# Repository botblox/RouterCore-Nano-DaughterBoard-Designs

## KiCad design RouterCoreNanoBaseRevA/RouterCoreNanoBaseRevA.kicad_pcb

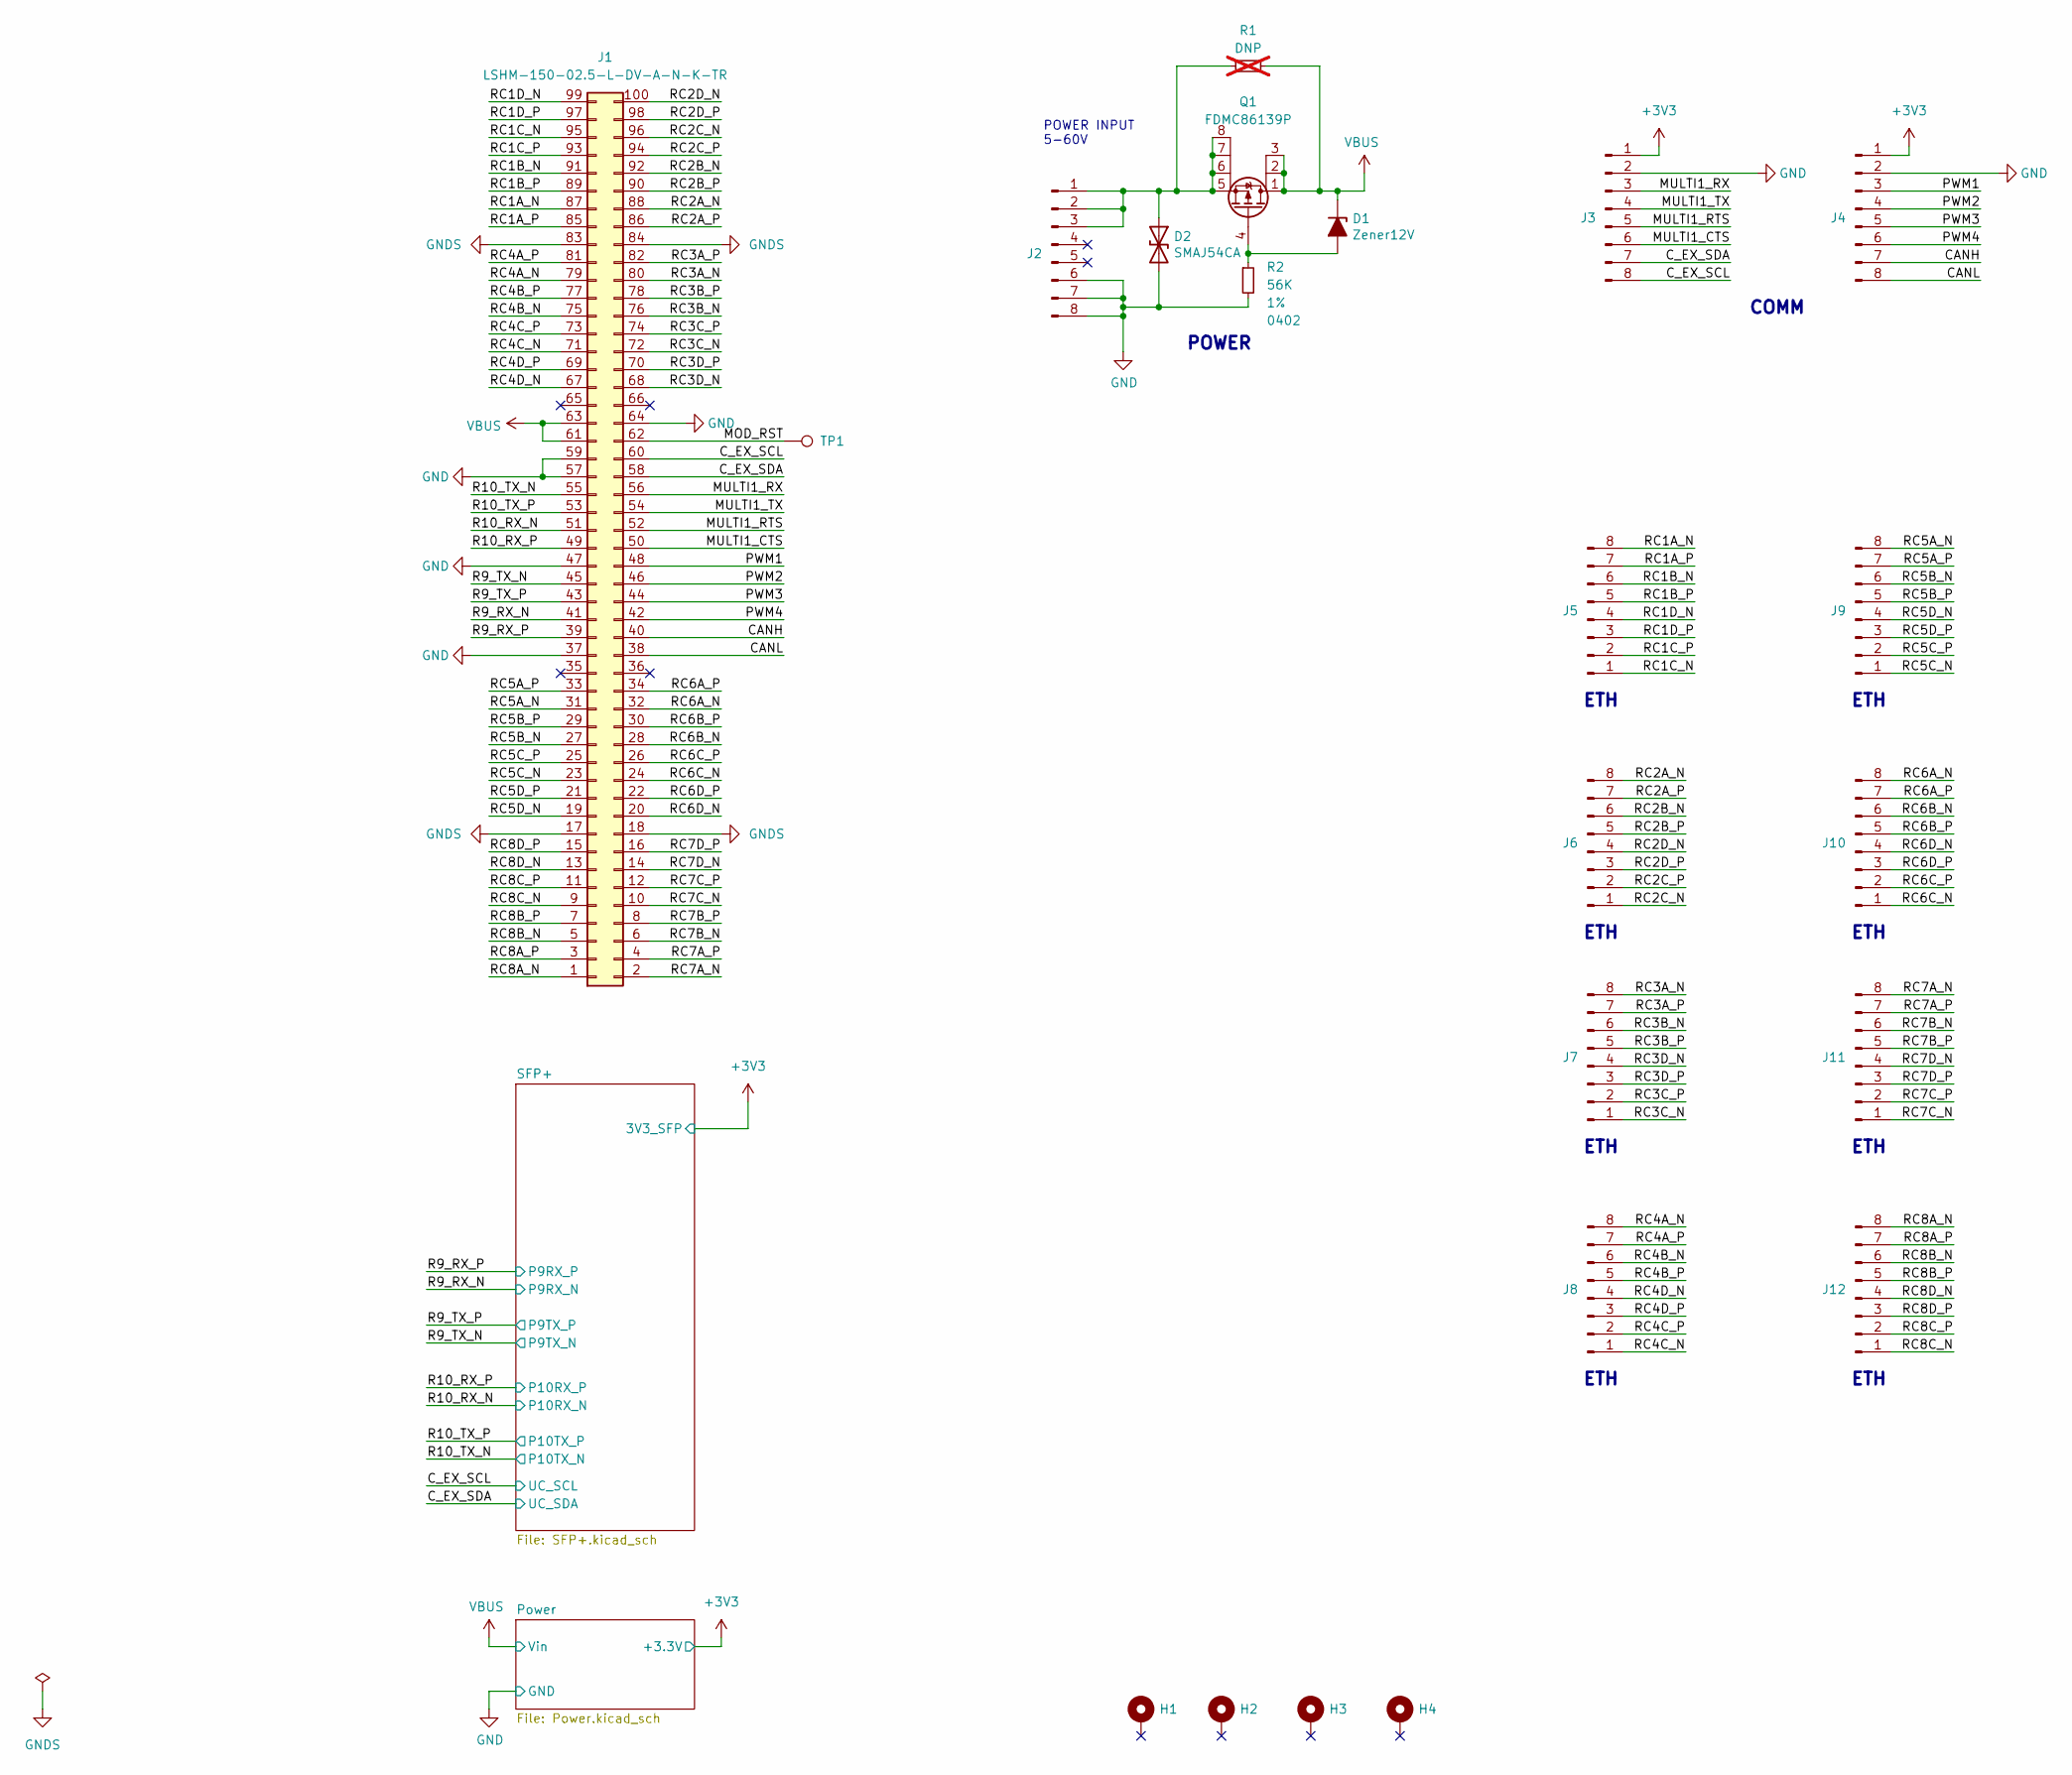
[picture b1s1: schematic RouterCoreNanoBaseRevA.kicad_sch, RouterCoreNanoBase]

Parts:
D1: Zener12V; D_SOD-323; VOLTAGE 12V; MFG1_PART# MM3Z12VT1G; JLC C236177
D2: SMAJ54CA; D_SMA; VOLTAGE 54V; MFG1_PART# SMAJ54CA; JLC C2649855
H1, H2, H3, H4: SMTWE2050MTJ; MountingHole_M2_9774050243R_SMTWE2050MTJ; MFG1_PART# SMTWE2050MTJ; JLC C2928183
J1: LSHM-150-02.5-L-DV-A-N-K-TR; Samtec_LSHM-150-xx.x-x-DV-N_2x50_P0.50mm_Vertical; MFG1_PART# LSHM-150-02.5-L-DV-A-N-K-TR; JLC C2940507
J2, J3, J4, J5, J6, J7, J8, J9, J10, J11, J12: 2147210080; Molex_Zero-Hachi_214721-00XX_1x08_P0.8mm_Horizontal; MFG1_PART# 2147210080; JLC C5492017
Q1: FDMC86139P; VSON-8_3.3x3.3mm_P0.65mm_FDMC86139P; VOLTAGE 100V; MFG1_PART# FDMC86139P; JLC C463243
R1: DNP; R_0603_1608Metric; MFG1_PART# DNP; not fitted
R2: 56K; R_0402_1005Metric; TOLERANCE 1%; MFG1_PART# RC0402FR-0756KL; JLC C114756
TP1: TP; TestPoint_Pad_D1.0mm; MFG1_PART# DNP

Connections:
+3V3: J3.1, J4.1; also elsewhere on the board
/CANH: J1.40, J4.7
/CANL: J1.38, J4.8
/C_EX_SCL: J1.60, J3.8; also elsewhere on the board
/C_EX_SDA: J1.58, J3.7; also elsewhere on the board
/MOD_RST: J1.62, TP1.1
/MULTI1_CTS: J1.50, J3.6
/MULTI1_RTS: J1.52, J3.5
/MULTI1_RX: J1.56, J3.3
/MULTI1_TX: J1.54, J3.4
/PWM1: J1.48, J4.3
/PWM2: J1.46, J4.4
/PWM3: J1.44, J4.5
/PWM4: J1.42, J4.6
/R9_RX_N: J1.41; also elsewhere on the board
/R9_RX_P: J1.39; also elsewhere on the board
/R9_TX_N: J1.45; also elsewhere on the board
/R9_TX_P: J1.43; also elsewhere on the board
/R10_RX_N: J1.51; also elsewhere on the board
/R10_RX_P: J1.49; also elsewhere on the board
/R10_TX_N: J1.55; also elsewhere on the board
/R10_TX_P: J1.53; also elsewhere on the board
/RC1A_N: J1.87, J5.8
/RC1A_P: J1.85, J5.7
/RC1B_N: J1.91, J5.6
/RC1B_P: J1.89, J5.5
/RC1C_N: J1.95, J5.1
/RC1C_P: J1.93, J5.2
/RC1D_N: J1.99, J5.4
/RC1D_P: J1.97, J5.3
/RC2A_N: J1.88, J6.8
/RC2A_P: J1.86, J6.7
/RC2B_N: J1.92, J6.6
/RC2B_P: J1.90, J6.5
/RC2C_N: J1.96, J6.1
/RC2C_P: J1.94, J6.2
/RC2D_N: J1.100, J6.4
/RC2D_P: J1.98, J6.3
/RC3A_N: J1.80, J7.8
/RC3A_P: J1.82, J7.7
/RC3B_N: J1.76, J7.6
/RC3B_P: J1.78, J7.5
/RC3C_N: J1.72, J7.1
/RC3C_P: J1.74, J7.2
/RC3D_N: J1.68, J7.4
/RC3D_P: J1.70, J7.3
/RC4A_N: J1.79, J8.8
/RC4A_P: J1.81, J8.7
/RC4B_N: J1.75, J8.6
/RC4B_P: J1.77, J8.5
/RC4C_N: J1.71, J8.1
/RC4C_P: J1.73, J8.2
/RC4D_N: J1.67, J8.4
/RC4D_P: J1.69, J8.3
/RC5A_N: J1.31, J9.8
/RC5A_P: J1.33, J9.7
/RC5B_N: J1.27, J9.6
/RC5B_P: J1.29, J9.5
/RC5C_N: J1.23, J9.1
/RC5C_P: J1.25, J9.2
/RC5D_N: J1.19, J9.4
/RC5D_P: J1.21, J9.3
/RC6A_N: J1.32, J10.8
/RC6A_P: J1.34, J10.7
/RC6B_N: J1.28, J10.6
/RC6B_P: J1.30, J10.5
/RC6C_N: J1.24, J10.1
/RC6C_P: J1.26, J10.2
/RC6D_N: J1.20, J10.4
/RC6D_P: J1.22, J10.3
/RC7A_N: J1.2, J11.8
/RC7A_P: J1.4, J11.7
/RC7B_N: J1.6, J11.6
/RC7B_P: J1.8, J11.5
/RC7C_N: J1.10, J11.1
/RC7C_P: J1.12, J11.2
/RC7D_N: J1.14, J11.4
/RC7D_P: J1.16, J11.3
/RC8A_N: J1.1, J12.8
/RC8A_P: J1.3, J12.7
/RC8B_N: J1.5, J12.6
/RC8B_P: J1.7, J12.5
/RC8C_N: J1.9, J12.1
/RC8C_P: J1.11, J12.2
/RC8D_N: J1.13, J12.4
/RC8D_P: J1.15, J12.3
GND: D2.2 (A2), J1.37, J1.47, J1.57, J1.59, J1.64, J2.6, J2.7, J2.8, J3.2, J4.2, R2.2; also elsewhere on the board
GNDS: J1.17, J1.18, J1.83, J1.84
unnamed: D1.2 (A), Q1.4 (G), R2.1
unnamed: D2.1 (A1), J2.1, J2.2, J2.3, Q1.5 (D), Q1.6 (D), Q1.7 (D), Q1.8 (D), R1.1
VBUS: D1.1 (K), J1.61, J1.63, Q1.1 (S), Q1.2 (S), Q1.3 (S), R1.2; also elsewhere on the board

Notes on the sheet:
ETH
POWER
COMM
POWER INPUT 5-60V

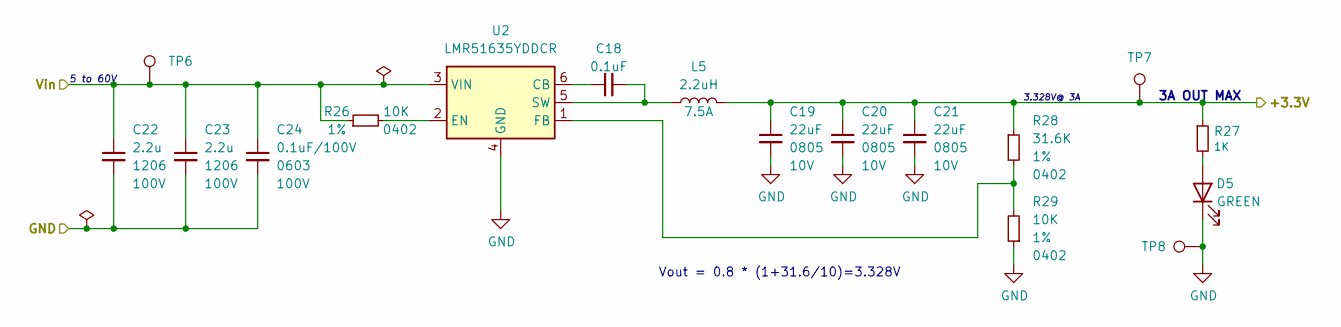
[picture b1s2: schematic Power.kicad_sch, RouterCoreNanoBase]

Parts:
C18: 0.1uF; C_0402_Small; VOLTAGE 50V; TOLERANCE 10%; MFG1_PART# GCM155R71H104KE02D; LCSC# C85858
C19, C20, C21: 22uF; C_0805_2012Metric; VOLTAGE 10V; TOLERANCE 20%; MFG1_PART# GRM21BZ71A226ME15L; LCSC# C907991
C22, C23: 2.2u; C_1206_Small; VOLTAGE 100V; TOLERANCE 10%; MFG1_PART# CL31B225KCHSNNE; LCSC# C170101
C24: 0.1uF/100V; C_0603_Small; VOLTAGE 100V; TOLERANCE 10%; MFG1_PART# CC0603KRX7R0BB104; LCSC# C113803
D5: GREEN; LED_0402_1005Metric; MFG2_PART# APHHS1005CGCK; LCSC# C264408
L5: 2.2uH; L_Sunlord_MWSA0503S; TOLERANCE ±20%; MFG1_PART# MWSA0503S-2R2MT; LCSC# C408408
R26, R29: 10K; R_0402_1005Metric; TOLERANCE 1%; MFG1_PART# RC0402FR-0710KL; LCSC# C60490
R27: 1K; R_0402_1005Metric; TOLERANCE 1%; MFG1_PART# RC0402FR-071KL; LCSC# C106235
R28: 31.6K; R_0402_1005Metric; TOLERANCE 1%; MFG1_PART# RC0402FR-0731K6L; LCSC# C276265
TP6, TP7, TP8: TP; TestPoint_Pad_D1.0mm; MFG1_PART# DNP
U2: LMR51635YDDCR; SOT-23-6; MFG1_PART# LMR51635YDDCR; JLC C45262770

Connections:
+3V3: C19.1, C20.1, C21.1, L5.2, R27.1, R28.1, TP7.1; also elsewhere on the board
GND: C19.2, C20.2, C21.2, C22.2, C23.2, C24.2, D5.1 (K), R29.1, TP8.1, U2.4 (GND); also elsewhere on the board
unnamed: D5.2 (A), R27.2
unnamed: C18.1, U2.6 (CB)
unnamed: R26.2, U2.2 (EN)
unnamed: R28.2, R29.2, U2.1 (FB)
unnamed: C18.2, L5.1, U2.5 (SW)
VBUS: C22.1, C23.1, C24.1, R26.1, TP6.1, U2.3 (VIN); also elsewhere on the board

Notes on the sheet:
3A OUT MAX
5 to 60V
Vout = 0.8 * (1+31.6/10)=3.328V
3.328V@ 3A

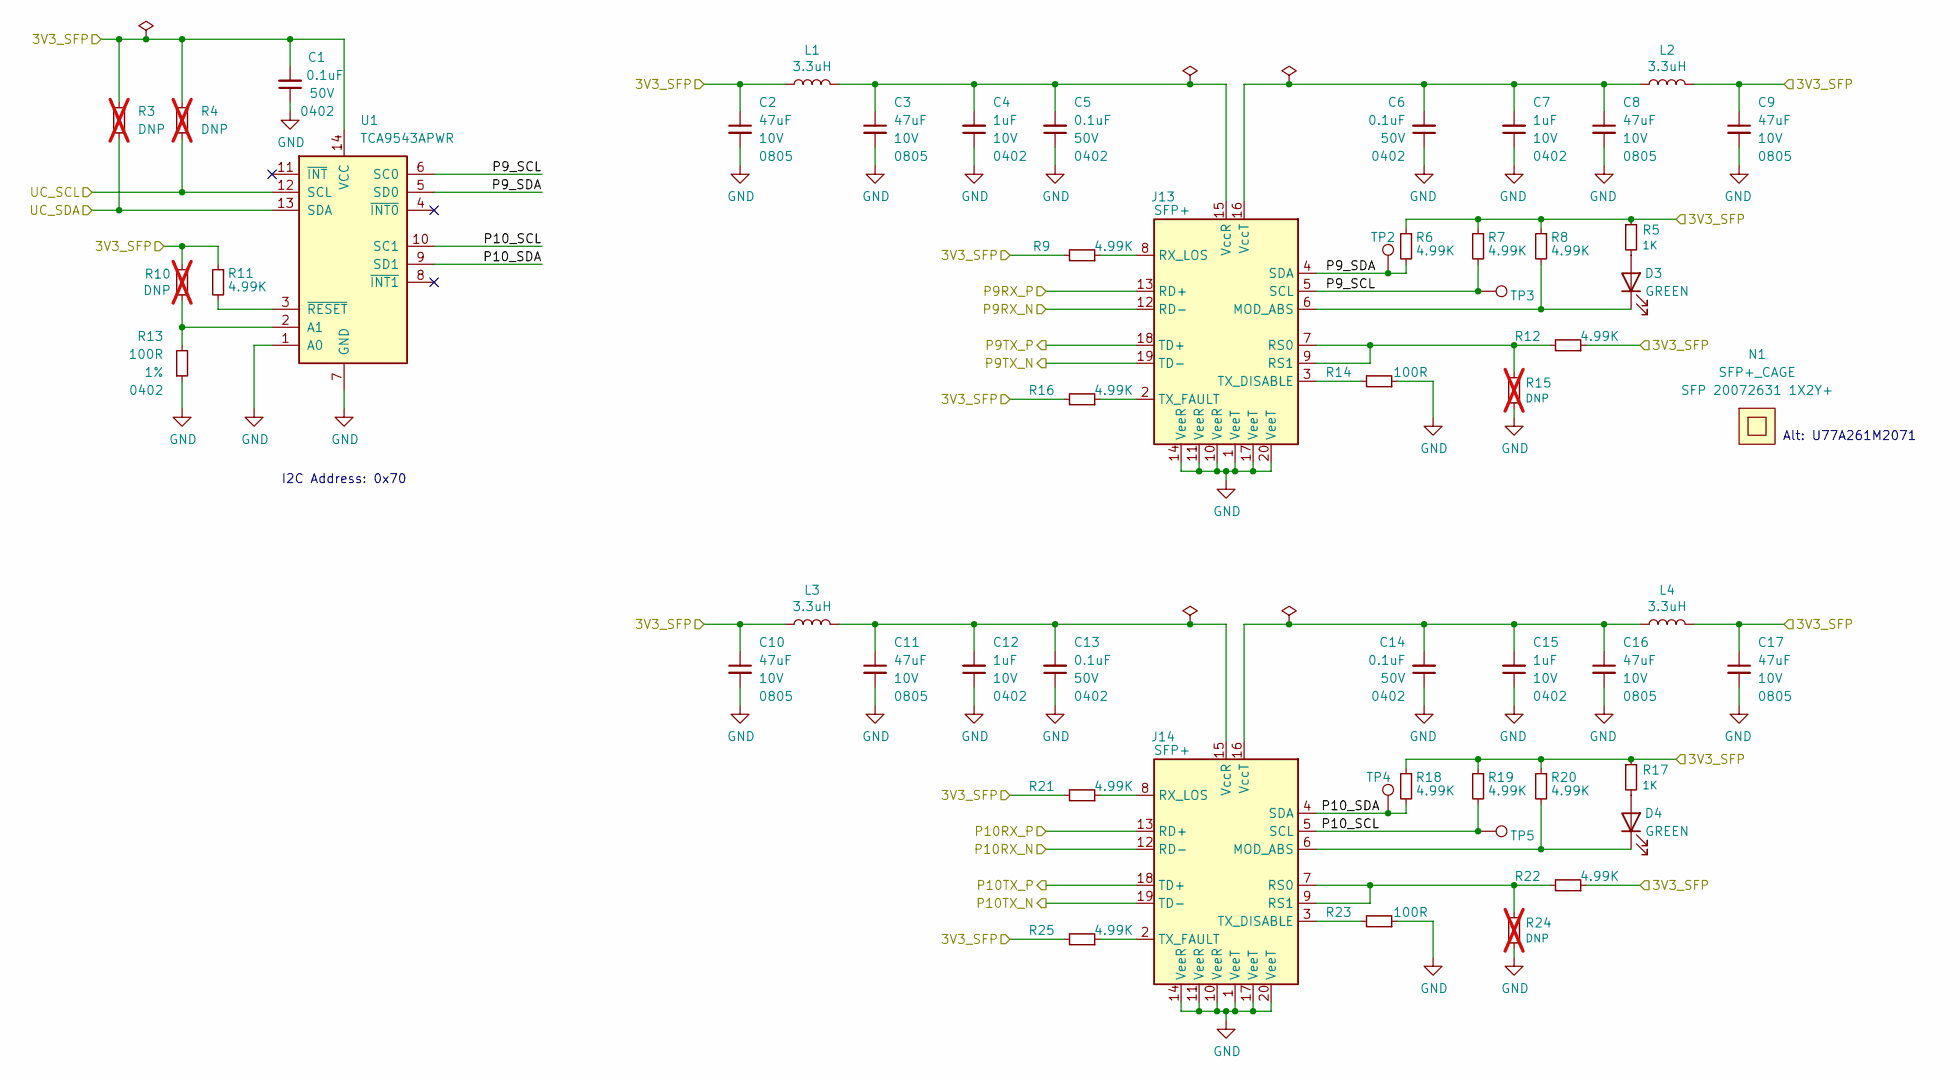
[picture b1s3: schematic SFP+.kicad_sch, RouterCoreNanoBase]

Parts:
C1, C5, C6, C13, C14: 0.1uF; C_0402_Small; VOLTAGE 50V; TOLERANCE 10%; MFG1_PART# GCM155R71H104KE02D; LCSC# C85858
C2, C3, C8, C9, C10, C11, C16, C17: 47uF; C_0805_2012Metric; VOLTAGE 10V; TOLERANCE 20%; MFG1_PART# C2012X5R1A476MTJ00E; LCSC# C76636
C4, C7, C12, C15: 1uF; C_0402_Small; VOLTAGE 10V; TOLERANCE 10%; MFG1_PART# GRM155C81A105KA12D; LCSC# C162161
D3, D4: GREEN; LED_0402_1005Metric; MFG2_PART# APHHS1005CGCK; LCSC# C264408
J13, J14: SFP+; Connector_SFP; MFG1_PART# 0744410001; LCSC# C277615
L1, L2, L3, L4: 3.3uH; L_1008_2520Metric; MFG1_PART# DFE252012F-3R3M=P2; LCSC# C2041573
N1: SFP+_CAGE; AMPHENOL_U77A261M2071; MFG1_PART# SFP 20072631 1X2Y+; JLC C42931391
R3, R4, R10, R15, R24: DNP; R_0402_1005Metric; MFG1_PART# DNP; not fitted
R5, R17: 1K; R_0402_1005Metric; TOLERANCE 1%; MFG1_PART# RC0402FR-071KL; LCSC# C106235
R6, R7, R8, R9, R11, R12, R16, R18, R19, R20, R21, R22, R25: 4.99K; R_0402_1005Metric; TOLERANCE 1%; MFG1_PART# RC0402FR-074K99L; LCSC# C137965
R13, R14, R23: 100R; R_0402_1005Metric; TOLERANCE 1%; MFG1_PART# RC0402FR-07100RL; LCSC# C106232
TP2, TP3, TP4, TP5: TP; TestPoint_Pad_D1.0mm; MFG1_PART# DNP
U1: TCA9543APWR; TSSOP-14_4.4x5mm_P0.65mm; MFG1_PART# TCA9543APWR; JLC C2653307

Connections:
+3V3: C1.2, C2.1, C9.1, C10.1, C17.1, L1.1, L2.1, L3.1, L4.1, R3.1, R4.1, R5.1, R6.1, R7.1, R8.1, R9.2, R10.2, R11.1, R12.1, R16.2, R17.1, R18.1, R19.1, R20.1, R21.2, R22.1, R25.2, U1.14 (VCC); also elsewhere on the board
/C_EX_SCL: R4.2, U1.12 (SCL); also elsewhere on the board
/C_EX_SDA: R3.2, U1.13 (SDA); also elsewhere on the board
/R9_RX_N: J13.12 (RD-); also elsewhere on the board
/R9_RX_P: J13.13 (RD+); also elsewhere on the board
/R9_TX_N: J13.19 (TD-); also elsewhere on the board
/R9_TX_P: J13.18 (TD+); also elsewhere on the board
/R10_RX_N: J14.12 (RD-); also elsewhere on the board
/R10_RX_P: J14.13 (RD+); also elsewhere on the board
/R10_TX_N: J14.19 (TD-); also elsewhere on the board
/R10_TX_P: J14.18 (TD+); also elsewhere on the board
/SFP+/P9_SCL: J13.5 (SCL), R7.2, TP3.1, U1.6 (SC0)
/SFP+/P9_SDA: J13.4 (SDA), R6.2, TP2.1, U1.5 (SD0)
/SFP+/P10_SCL: J14.5 (SCL), R19.2, TP5.1, U1.10 (SC1)
/SFP+/P10_SDA: J14.4 (SDA), R18.2, TP4.1, U1.9 (SD1)
GND: C1.1, C2.2, C3.2, C4.1, C5.1, C6.1, C7.1, C8.2, C9.2, C10.2, C11.2, C12.1, C13.1, C14.1, C15.1, C16.2, C17.2, J13.1 (VeeT), J13.10 (VeeR), J13.11 (VeeR), J13.14 (VeeR), J13.17 (VeeT), J13.20 (VeeT), J14.1 (VeeT), J14.10 (VeeR), J14.11 (VeeR), J14.14 (VeeR), J14.17 (VeeT), J14.20 (VeeT), R13.1, R14.1, R15.1, R23.1, R24.1, U1.1 (A0), U1.7 (GND); also elsewhere on the board
unnamed: D3.2 (A), R5.2
unnamed: D3.1 (K), J13.6 (MOD_ABS), R8.2
unnamed: D4.2 (A), R17.2
unnamed: D4.1 (K), J14.6 (MOD_ABS), R20.2
unnamed: J13.7 (RS0), J13.9 (RS1), R12.2, R15.2
unnamed: J13.8 (RX_LOS), R9.1
unnamed: J13.3 (TX_DISABLE), R14.2
unnamed: J13.2 (TX_FAULT), R16.1
unnamed: C3.1, C4.2, C5.2, J13.15 (VccR), L1.2
unnamed: C6.2, C7.2, C8.1, J13.16 (VccT), L2.2
unnamed: J14.7 (RS0), J14.9 (RS1), R22.2, R24.2
unnamed: J14.8 (RX_LOS), R21.1
unnamed: J14.3 (TX_DISABLE), R23.2
unnamed: J14.2 (TX_FAULT), R25.1
unnamed: C11.1, C12.2, C13.2, J14.15 (VccR), L3.2
unnamed: C14.2, C15.2, C16.1, J14.16 (VccT), L4.2
unnamed: R10.1, R13.2, U1.2 (A1)
unnamed: R11.2, U1.3 (~RESET)

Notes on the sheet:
Alt: U77A261M2071
I2C Address: 0x70

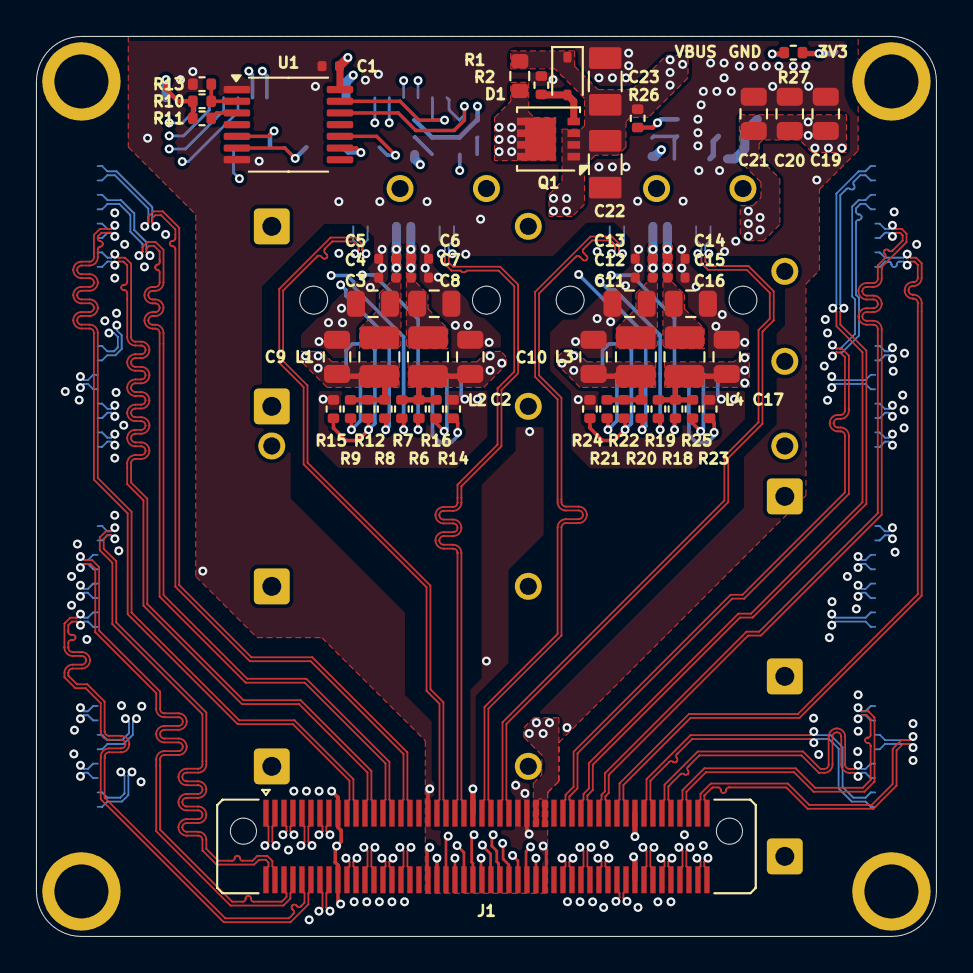
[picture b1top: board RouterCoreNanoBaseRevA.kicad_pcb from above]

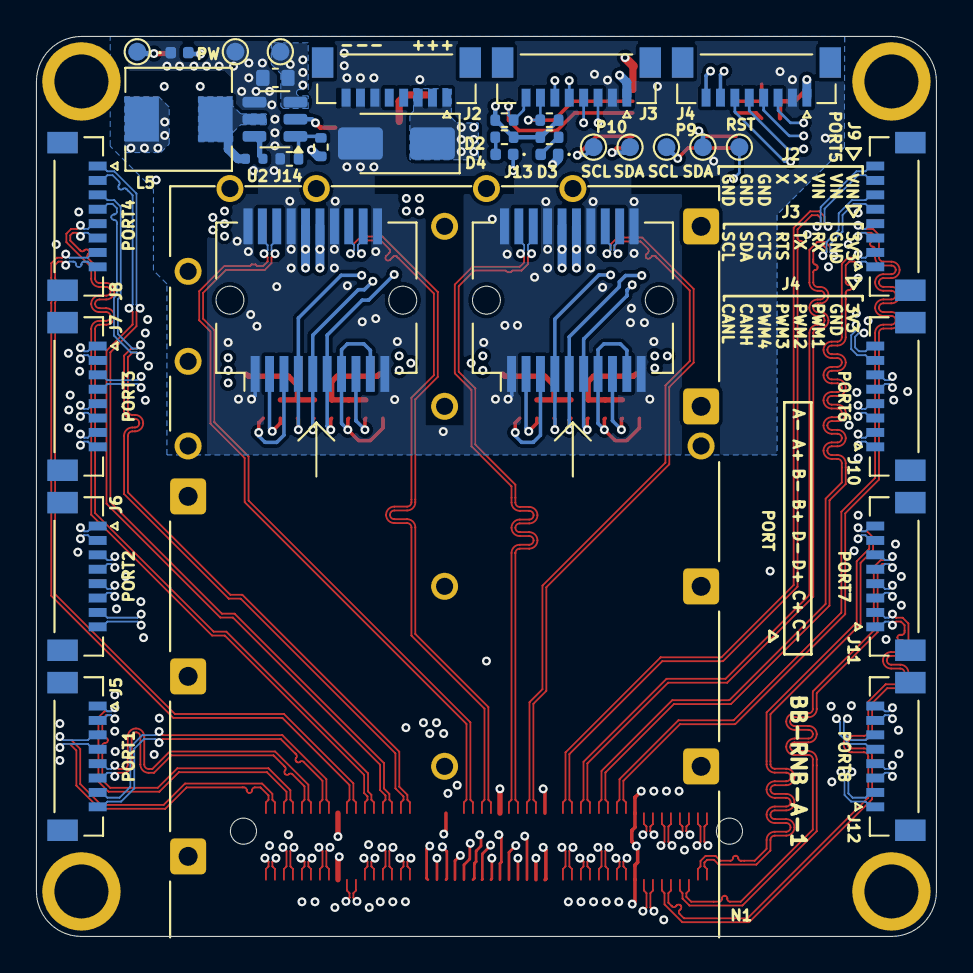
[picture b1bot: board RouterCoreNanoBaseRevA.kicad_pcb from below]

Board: 6 copper layers, 50.0 x 50.0 mm, 93 parts (36 on the bottom side), 118 nets.

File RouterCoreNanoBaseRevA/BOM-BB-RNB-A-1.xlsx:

No | Ref | Value | Description | Manufacturer | Manufacturer Part Number | LCSC | Footprint | Quantity | Supplier 1 | Cost @10pcs | Cost @1000pcs
1 | C1, C5, C6, C13, C14, C18, | 0.1uF | CAP CER 0.1UF 50V X7R 0402 | Murata Electronics | GCM155R71H104KE02D | C85858 | Kpk:C_0402_Small | 6 | LCSC | 8.5000000000000006E-3 | 6.7000000000000002E-3
2 | C2, C3, C8, C9, C10, C11, C16, C17, | 47uF | CAP CER 47UF 10V X5R 0805 | TDK | C2012X5R1A476MTJ00E | C76636 | Capacitor_SMD:C_0805_2012Metric | 8 | LCSC | 0.1986 | 0.122
3 | C4, C7, C12, C15, | 1uF | CAP CER 1UF 10V X6S 0402 | Murata Electronics | GRM155C81A105KA12D | C162161 | Kpk:C_0402_Small | 4 | LCSC | 2.8500000000000001E-2 | 2.0400000000000001E-2
4 | C19, C20, C21, | 22uF | CAP CER 22UF 10V X7R 0805 | Murata Electronics | GRM21BZ71A226ME15L | C907991 | Capacitor_SMD:C_0805_2012Metric | 3 | LCSC | 0.25509999999999999 | 0.17519999999999999
5 | C22, C23, | 2.2u | CAP CER 2.2UF 100V X7R 1206 | Samsung Electro-Mechanics | CL31B225KCHSNNE | C170101 | Kpk:C_1206_Small | 2 | LCSC | 0.13389999999999999 | 8.2600000000000007E-2
6 | C24, | 0.1uF/100V | CAP CER 0.1UF 100V X7R 0603 | YAGEO | CC0603KRX7R0BB104 | C113803 | Kpk:C_0603_Small | 1 | LCSC | 1.1599999999999999E-2 | 8.8000000000000005E-3
7 | D1, | Zener12V | DIODE ZENER 12V 300MW SOD323 | ON Semiconductor | MM3Z12VT1G | C236177 | Diode_SMD:D_SOD-323 | 1 | LCSC | 4.7399999999999998E-2 | 3.3700000000000001E-2
8 | D2, | SMAJ54CA | TVS DIODE 54V 87.1V DO214AC | Littelfuse | SMAJ54CA | C2649855 | Diode_SMD:D_SMA | 1 | LCSC | 0.1152 | 0.1104
9 | D3, D4, D5, | GREEN | LED GREEN CLEAR CHIP SMD | Everlight Elec | 16-213SYGC/S530-E3/TR8 | C264408 | LED_SMD:LED_0402_1005Metric | 3 | LCSC | 2.1100000000000001E-2 | 1.35E-2
10 | H1, H2, H3, H4, | SMTWE2050MTJ | ROUND STANDOFF M2X0.4 STEEL 5MM | Sinhoo | SMTWE2050MTJ | C2928183 | Kpk:MountingHole_M2_9774050243R_SMTWE2050MTJ | 4 | LCSC | 0.1076 | 0.1017
11 | J1, | LSHM-150-02.5-L-DV-A-N-K-TR | CONN SELF-MATE 100POS SMD GOLD | Samtec Inc. | LSHM-150-02.5-L-DV-A-N-K-TR | C2940507 | Connector_Samtec:Samtec_LSHM-150-xx.x-x-DV-N_2x50_P0.50mm_Vertical | 1 | Digikey | 6.3710000000000004 | 4.6400199999999998
12 | J2, J3, J4, J5, J6, J7, J8, J9, J10, J11, J12, | 2147210080 | ZERO-HACHI 8P 0.8 HDR SR RA ETP | Molex | 2147210080 | C5492017 | Kpk:Molex_Zero-Hachi_214721-00XX_1x08_P0.8mm_Horizontal | 11 | Digikey | 1.3109999999999999 | 0.94681000000000004
13 | J13, J14, | SFP+ | CONN SFP+ RCPT 20POS SLD R/A SMD | Molex | 744410001 | C277615 | Kpk:Connector_SFP | 2 | LCSC | 0.65969999999999995 | 0.43
14 | L1, L2, L3, L4, | 3.3uH | FIXED IND 3.3UH 1.8A 135MOHM SMD | Murata Electronics | DFE252012F-3R3M=P2 | C2041573 | Inductor_SMD:L_1008_2520Metric | 4 | LCSC | 0.19700000000000001 | 0.14449999999999999
15 | L5, | 2.2uH | FIXED IND 2.2UH 7A 29 MOHM SMD | Shenzhen Sunlord Electronics Co., Ltd. | MWSA0503S-2R2MT | C408408 | Inductor_SMD:L_Sunlord_MWSA0503S | 1 | LCSC | 0.1542 | 0.1012
16 | N1, | SFP+_CAGE | CONN SFP+ CAGE 1X2 PRESS-FIT R/A | CND-tek | SFP 20072631 1X2Y+ | C42931391 | Kpk:AMPHENOL_U77A261M2071 | 1 | LCSC | 1.2274 | 0.85309999999999997
17 | Q1, | FDMC86139P | MOSFET P-CH 100V 4.4A/15A 8MLP | onsemi | FDMC86139P | C463243 | Kpk:VSON-8_3.3x3.3mm_P0.65mm_FDMC86139P | 1 | LCSC | 0.96860000000000002 | 0.61619999999999997
18 | R1, | DNP | DNP |  | DNP |  | Resistor_SMD:R_0603_1608Metric | 1
19 | R2, | 56K | RES SMD 56K OHM 1% 1/16W 0402 | YAGEO | RC0402FR-0756KL | C114756 | Resistor_SMD:R_0402_1005Metric | 1 | LCSC | 2.5999999999999999E-3 | 2E-3
20 | R3, R4, R10, R15, R24, | DNP | DNP |  | DNP |  | Resistor_SMD:R_0402_1005Metric | 5
21 | R5, R17, R27, | 1K | RES SMD 1K OHM 1% 1/16W 0402 | YAGEO | RC0402FR-071KL | C106235 | Resistor_SMD:R_0402_1005Metric | 3 | LCSC | 3.8E-3 | 2.8999999999999998E-3
22 | R6, R7, R8, R9, R11, R12, R16, R18, R19, R20, R21, R22, R25, | 4.99K | RES 4.99K OHM 1% 1/16W 0402 | YAGEO | RC0402FR-074K99L | C137965 | Resistor_SMD:R_0402_1005Metric | 13 | LCSC | 1.6999999999999999E-3 | 1.4E-3
23 | R13, R14, R23, | 100R | RES 100 OHM 1% 1/16W 0402 | YAGEO | RC0402FR-07100RL | C106232 | Resistor_SMD:R_0402_1005Metric | 3 | LCSC | 2.2000000000000001E-3 | 1.8E-3
24 | R26, R29, | 10K | RES SMD 10K OHM 1% 1/16W 0402 | YAGEO | RC0402FR-0710KL | C60490 | Resistor_SMD:R_0402_1005Metric | 2 | LCSC | 2.3E-3 | 1.9E-3
25 | R28, | 31.6K | RES 31.6K OHM 1% 1/16W 0402 | YAGEO | RC0402FR-0731K6L | C276265 | Resistor_SMD:R_0402_1005Metric | 1 | LCSC | 1.1999999999999999E-3 | 1E-3
26 | TP1, TP2, TP3, TP4, TP5, TP6, TP7, TP8, | TP | TestPoint |  | DNP |  | TestPoint:TestPoint_Pad_D1.0mm | 8
27 | U1, | TCA9543APWR | IC BUS SWITCH 2 X 1:2 14-TSSOP | Texas Instruments | TCA9543APWR | C2653307 | Package_SO:TSSOP-14_4.4x5mm_P0.65mm | 1 | LCSC | 0.73060000000000003 | 0.52539999999999998
28 | U2, | LMR51635YDDCR | SIMPLE SWITCHER SYNCHRONOUS BUCK | Texas Instruments | LMR51635YDDCR | C45262770 | Package_TO_SOT_SMD:SOT-23-6 | 1 | LCSC | 1.5996999999999999 | 1.1365000000000001
 |  |  |  |  |  |  |  |  |  | 31.083199999999994 | 22.153230000000004
